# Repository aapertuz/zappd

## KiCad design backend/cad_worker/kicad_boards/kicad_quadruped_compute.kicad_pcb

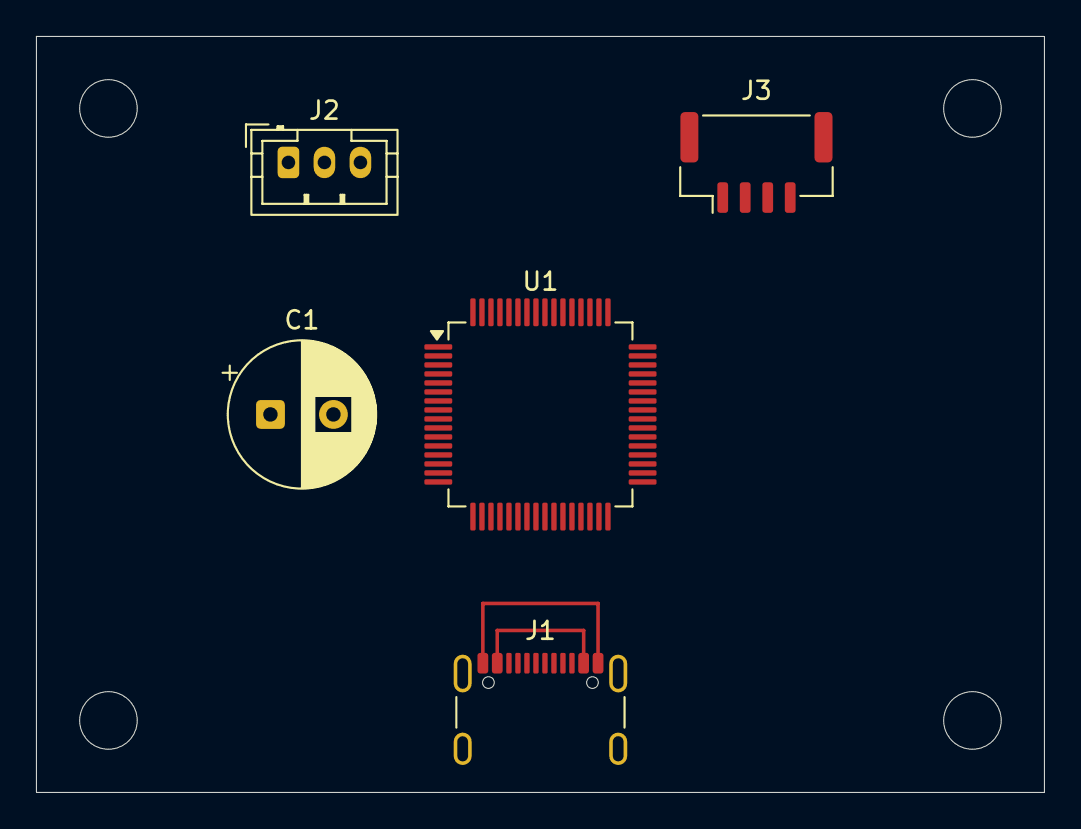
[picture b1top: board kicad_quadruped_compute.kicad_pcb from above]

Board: 2 copper layers, 56.0 x 42.0 mm, 9 parts (0 on the bottom side), 2 nets.

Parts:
C1: CP_Radial_D8.0mm_P3.50mm
H1, H2, H3, H4: MountingHole
J1: USB_C_Receptacle_GCT_USB4105-xx-A_16P_TopMnt_Hori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; USB_C_Receptacle_GCT_USB4105-xx-A_16P_TopMnt_Horizontal
J2: JST_PH_B3B-PH-K_1x03_P2.00mm_Vertical
J3: JST_GH_BM04B-GHS-TBT_1x04-1MP_P1.25mm_Vertical
U1: LQFP-64_10x10mm_P0.5mm

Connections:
GND: J1.A1, J1.A12, J1.B1, J1.B12
VBUS: J1.A4, J1.A9, J1.B4, J1.B9
